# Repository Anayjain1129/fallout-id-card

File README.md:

# fallout-id-card
This is a ID card made at Fallout First Day! 

# Schematics 

# PCB

# 3D View

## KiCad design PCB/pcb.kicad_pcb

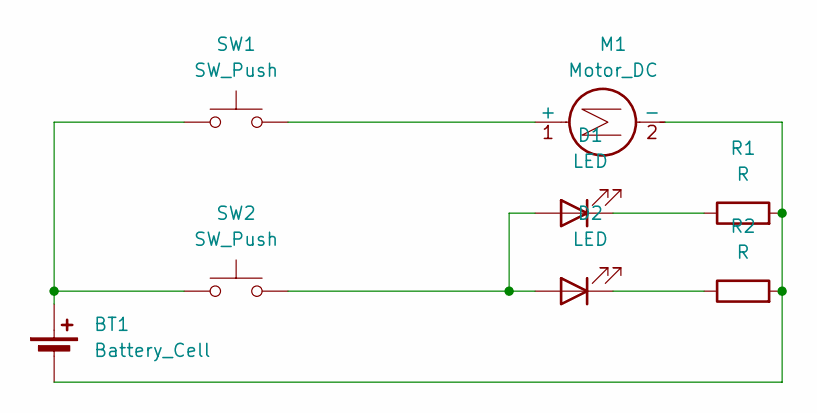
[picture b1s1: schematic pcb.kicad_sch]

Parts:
BT1: Battery_Cell; BatteryHolder_Keystone_3034_1x20mm
D1, D2: LED; LED_D5.0mm
M1: Motor_DC; PinHeader_1x02_P2.54mm_Vertical
R1, R2: R; R_Axial_DIN0207_L6.3mm_D2.5mm_P7.62mm_Horizontal
SW1, SW2: SW_Push; SW_PUSH_6mm

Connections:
unnamed: BT1.1 (+), SW1.1, SW2.1
unnamed: BT1.2 (-), M1.2 (-), R1.2, R2.2
unnamed: D1.2 (A), D2.2 (A), SW2.2
unnamed: D1.1 (K), R1.1
unnamed: D2.1 (K), R2.1
unnamed: M1.1 (+), SW1.2

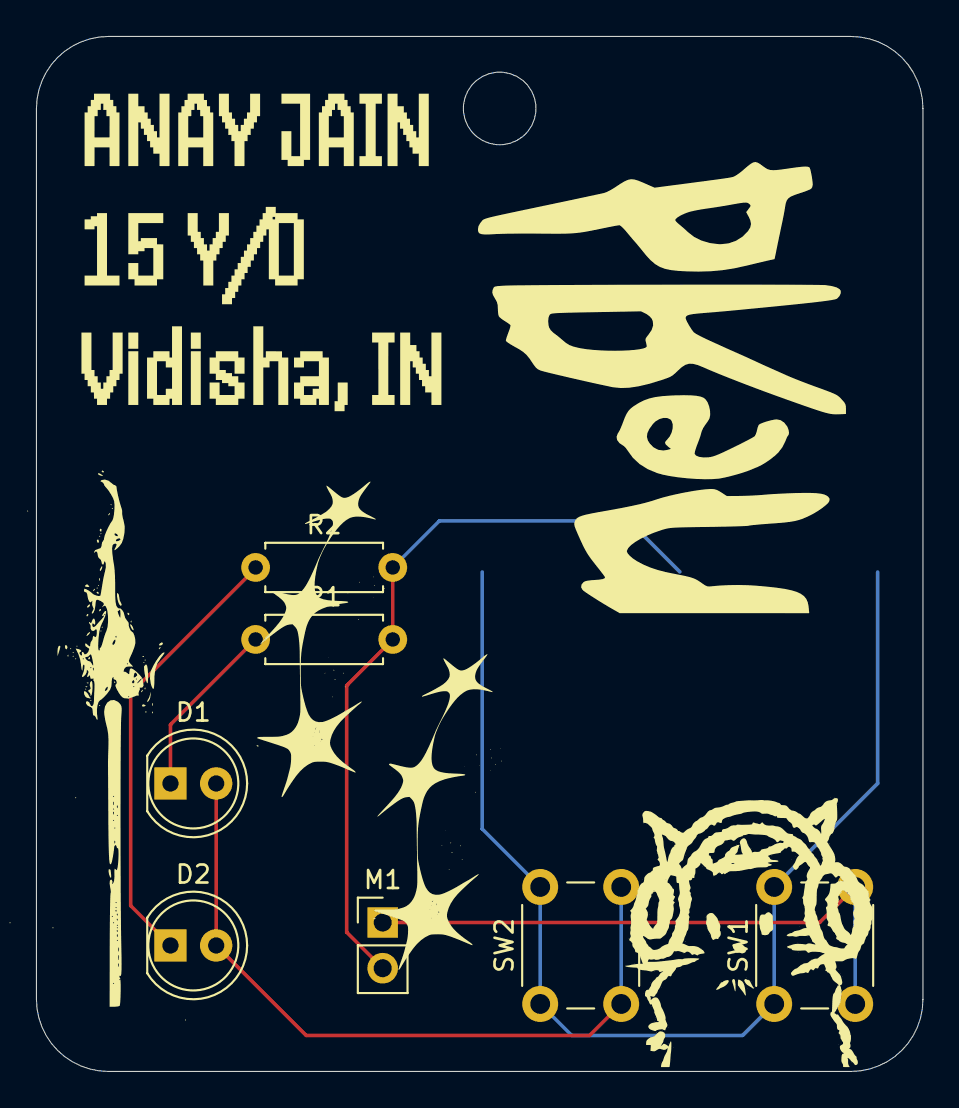
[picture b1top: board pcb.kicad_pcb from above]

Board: 2 copper layers, 49.2 x 57.5 mm, 8 parts (1 on the bottom side), 6 nets.
